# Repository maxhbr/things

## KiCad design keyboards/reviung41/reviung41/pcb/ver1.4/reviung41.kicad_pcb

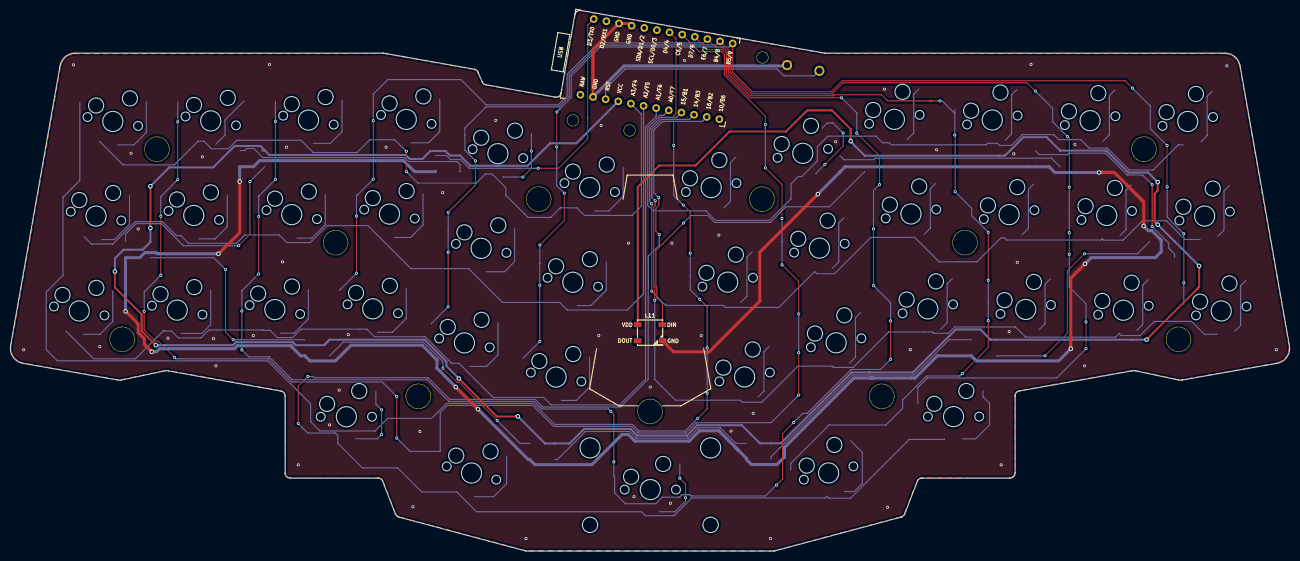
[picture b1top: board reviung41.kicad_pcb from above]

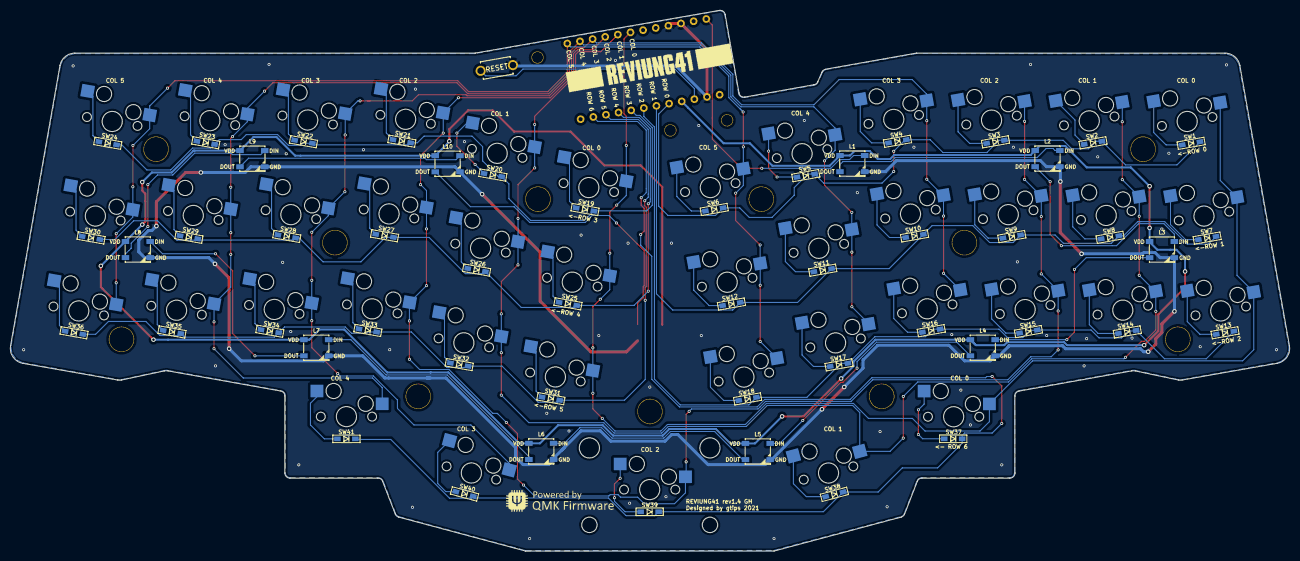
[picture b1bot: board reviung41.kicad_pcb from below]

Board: 2 copper layers, 253.3 x 107.1 mm, 109 parts (52 on the bottom side), 68 nets.

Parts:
D1, D2, D3, D4, D5, D6, D7, D8, D9, D10, D11, D12, D13, D14, D15, D16, D17, D18, D19, D20, D21, D22, D23, D24, D25, D26, D27, D28, D29, D30, D31, D32, D33, D34, D35, D36, D37, D38, D39, D40, D41: 1N4148W; D3_SMD_1side
H1: H1; HOLE
H2: H2; HOLE
H3: H3; HOLE
H4: H4; HOLE
H5: H5; HOLE
H6: H6; HOLE
H7: H7; HOLE
H8: H8; HOLE
H9: H9; HOLE
H10: H10; HOLE
H11: H11; HOLE
H12: H12; HOLE_2.2mm
H13: H13; HOLE_2.2mm
H14: H14; HOLE_2.2mm
L1, L2, L3, L4, L5, L6, L7, L8, L9, L10, L11: WS2812B; LED_WS2812B_PLCC4_5.0x5.0mm_P3.2mm
RESET1: SW_PUSH; ResetSW_1side
SW1, SW2, SW3, SW4, SW5, SW6, SW7, SW8, SW9, SW10, SW11, SW12, SW13, SW14, SW15, SW16, SW17, SW18, SW19, SW20, SW21, SW22, SW23, SW24, SW25, SW26, SW27, SW28, SW29, SW30, SW31, SW32, SW33, SW34, SW35, SW36, SW37, SW38, SW40, SW41: SW_PUSH; MXOnly-1U-Hotswap
SW39: SW_2U_PUSH; MXOnly-2U-Hotswap-ReversedStabilizers
U1: ProMicro

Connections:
GND: L1.3 (VSS), L2.3 (VSS), L3.3 (VSS), L4.3 (VSS), L5.3 (VSS), L6.3 (VSS), L7.3 (VSS), L8.3 (VSS), L9.3 (VSS), L10.3 (VSS), L11.3 (VSS), RESET1.2, U1.3 (GND), U1.4 (GND), U1.23 (GND)
LED: L1.4 (DIN), U1.1 (TX0/D3)
unnamed: D1.2 (A), SW1.2
unnamed: D2.2 (A), SW2.2
unnamed: D3.2 (A), SW3.2
unnamed: D4.2 (A), SW4.2
unnamed: D5.2 (A), SW5.2
unnamed: D6.2 (A), SW6.2
unnamed: D7.2 (A), SW7.2
unnamed: D8.2 (A), SW8.2
unnamed: D9.2 (A), SW9.2
unnamed: D10.2 (A), SW10.2
unnamed: D11.2 (A), SW11.2
unnamed: D12.2 (A), SW12.2
unnamed: D13.2 (A), SW13.2
unnamed: D14.2 (A), SW14.2
unnamed: D15.2 (A), SW15.2
unnamed: D16.2 (A), SW16.2
unnamed: D17.2 (A), SW17.2
unnamed: D18.2 (A), SW18.2
unnamed: D19.2 (A), SW19.2
unnamed: D20.2 (A), SW20.2
unnamed: D21.2 (A), SW21.2
unnamed: D22.2 (A), SW22.2
unnamed: D23.2 (A), SW23.2
unnamed: D24.2 (A), SW24.2
unnamed: D25.2 (A), SW25.2
unnamed: D26.2 (A), SW26.2
unnamed: D27.2 (A), SW27.2
unnamed: D28.2 (A), SW28.2
unnamed: D29.2 (A), SW29.2
unnamed: D30.2 (A), SW30.2
unnamed: D31.2 (A), SW31.2
unnamed: D32.2 (A), SW32.2
unnamed: D33.2 (A), SW33.2
unnamed: D34.2 (A), SW34.2
unnamed: D35.2 (A), SW35.2
unnamed: D36.2 (A), SW36.2
unnamed: D37.2 (A), SW37.2
unnamed: D38.2 (A), SW38.2
unnamed: D39.2 (A), SW39.2
unnamed: D40.2 (A), SW40.2
unnamed: D41.2 (A), SW41.2
unnamed: L1.2 (DOUT), L2.4 (DIN)
unnamed: L2.2 (DOUT), L3.4 (DIN)
unnamed: L3.2 (DOUT), L4.4 (DIN)
unnamed: L4.2 (DOUT), L5.4 (DIN)
unnamed: L5.2 (DOUT), L6.4 (DIN)
unnamed: L6.2 (DOUT), L7.4 (DIN)
unnamed: L7.2 (DOUT), L8.4 (DIN)
unnamed: L8.2 (DOUT), L9.4 (DIN)
unnamed: L10.2 (DOUT), L11.4 (DIN)
unnamed: L9.2 (DOUT), L10.4 (DIN)
VCC: L1.1 (VDD), L2.1 (VDD), L3.1 (VDD), L4.1 (VDD), L5.1 (VDD), L6.1 (VDD), L7.1 (VDD), L8.1 (VDD), L9.1 (VDD), L10.1 (VDD), L11.1 (VDD), U1.21 (VCC)
col0: SW1.1, SW7.1, SW13.1, SW19.1, SW25.1, SW31.1, SW37.1, U1.7 (4/D4)
col1: SW2.1, SW8.1, SW14.1, SW20.1, SW26.1, SW32.1, SW38.1, U1.8 (5/C6)
col2: SW3.1, SW9.1, SW15.1, SW21.1, SW27.1, SW33.1, SW39.1, U1.9 (6/D7)
col3: SW4.1, SW10.1, SW16.1, SW22.1, SW28.1, SW34.1, SW40.1, U1.10 (7/E6)
col4: SW5.1, SW11.1, SW17.1, SW23.1, SW29.1, SW35.1, SW41.1, U1.11 (8/B4)
col5: SW6.1, SW12.1, SW18.1, SW24.1, SW30.1, SW36.1, U1.12 (9/B5)
reset: RESET1.1, U1.22 (RST)
row0: D1.1 (K), D2.1 (K), D3.1 (K), D4.1 (K), D5.1 (K), D6.1 (K), U1.20 (F4/A3)
row1: D7.1 (K), D8.1 (K), D9.1 (K), D10.1 (K), D11.1 (K), D12.1 (K), U1.19 (F5/A2)
row2: D13.1 (K), D14.1 (K), D15.1 (K), D16.1 (K), D17.1 (K), D18.1 (K), U1.18 (F6/A1)
row3: D19.1 (K), D20.1 (K), D21.1 (K), D22.1 (K), D23.1 (K), D24.1 (K), U1.17 (F7/A0)
row4: D25.1 (K), D26.1 (K), D27.1 (K), D28.1 (K), D29.1 (K), D30.1 (K), U1.16 (B1/15)
row5: D31.1 (K), D32.1 (K), D33.1 (K), D34.1 (K), D35.1 (K), D36.1 (K), U1.15 (B3/14)
row6: D37.1 (K), D38.1 (K), D39.1 (K), D40.1 (K), D41.1 (K), U1.14 (B2/16)

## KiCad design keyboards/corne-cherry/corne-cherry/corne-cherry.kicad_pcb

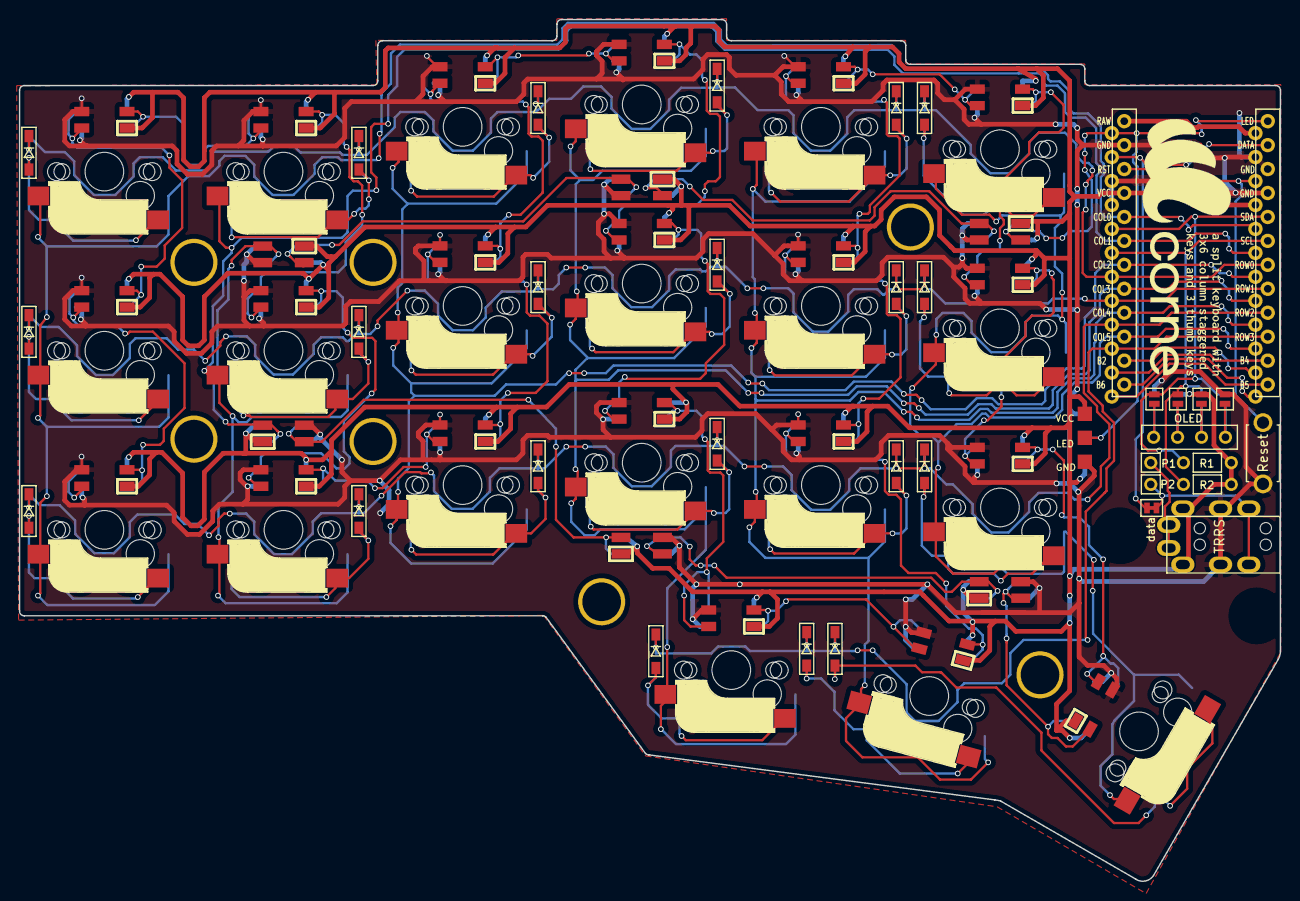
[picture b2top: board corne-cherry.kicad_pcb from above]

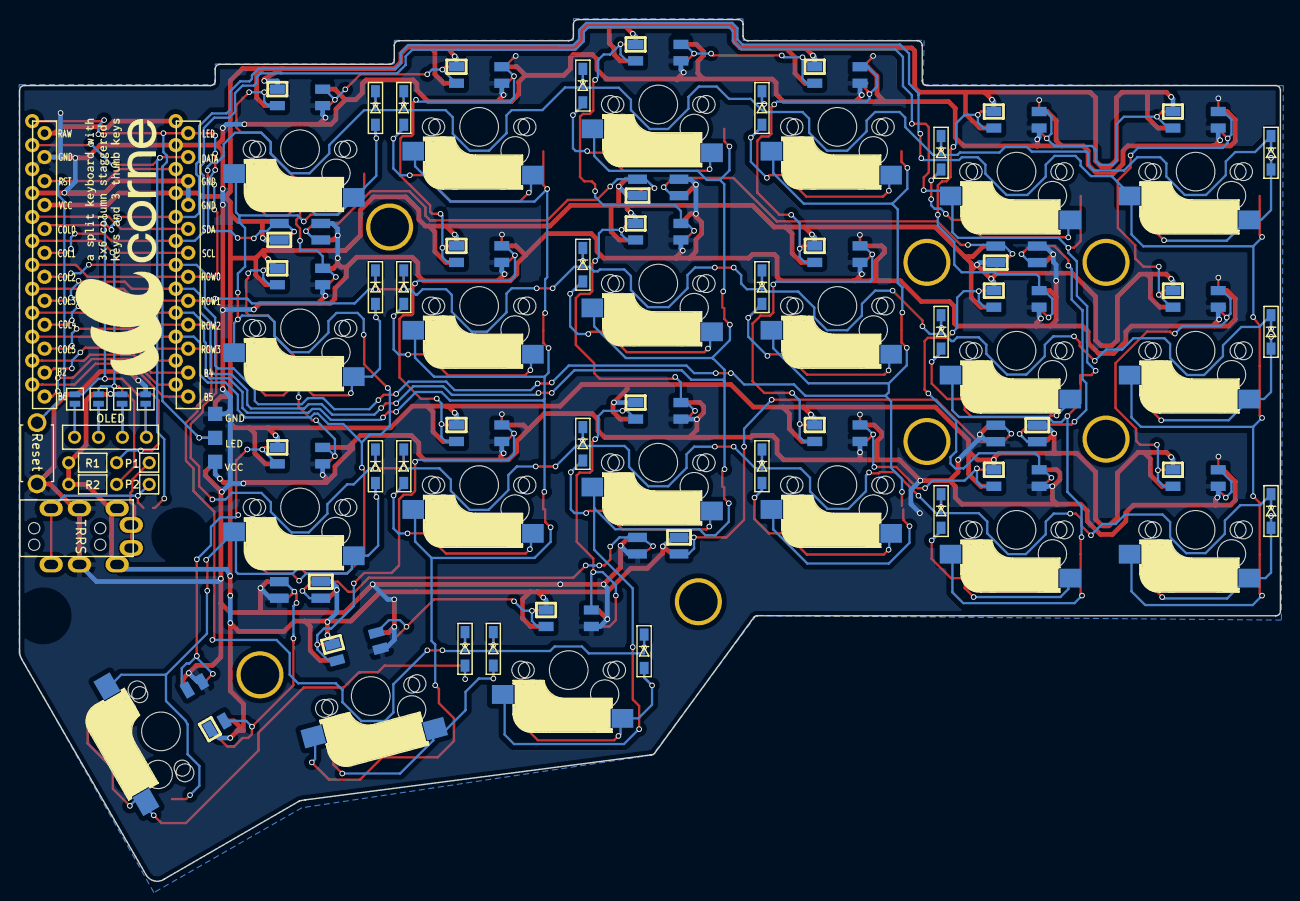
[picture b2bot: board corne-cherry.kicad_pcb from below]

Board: 2 copper layers, 133.8 x 91.4 mm, 87 parts (4 on the bottom side), 70 nets.

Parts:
D1, D2, D3, D4, D5, D6, D7, D8, D9, D10, D11, D12, D13, D14, D15, D16, D17, D18, D19, D20, D21: D; D3_SMD
J3: LED; StripLED_rev
JP2, JP3, JP4, JP5, JP6, JP7, JP8, JP9: Jumper
L1, L2, L3, L4, L5, L6, L7, L8, L9, L10, L11, L12, L13, L14, L15, L16, L17, L18, L19, L20, L21: SK6812MINI; SK6812MINI_rev
L22, L23, L24, L25, L26, L27: SK6812MINI; SK6812MINI_underglow_rev
OLED: OLED
P1, P2: i2c-pin; 1pin_conn
R1, R2: R
RSW1: Reset; ResetSW
SW1, SW2, SW3, SW4, SW5, SW6, SW7, SW8, SW9, SW10, SW11, SW12, SW13, SW14, SW15, SW16, SW17, SW18, SW19, SW20: SW_PUSH; CherryMX_MidHeight_Hotswap
SW21: SW_PUSH; CherryMX_MidHeight_Hotswap_1.5u
TRRS: MJ-4PP-9
U1: ProMicro; ProMicro_v2
data: JPC2

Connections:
GND: J3.1, JP2.1, JP9.1, L1.2, L2.2, L3.2, L4.2, L5.2, L6.2, L7.2, L8.2, L9.2, L10.2, L11.2, L12.2, L13.2, L14.2, L15.2, L16.2, L17.2, L18.2, L19.2, L20.2, L21.2, L22.2, L23.2, L24.2, L25.2, L26.2, L27.2, RSW1.2, TRRS.C, U1.3, U1.4, U1.23
LED: J3.2, L24.3, U1.1
unnamed: D1.2, SW1.2
unnamed: D2.2, SW2.2
unnamed: D3.2, SW3.2
unnamed: D4.2, SW4.2
unnamed: D5.2, SW5.2
unnamed: D6.2, SW6.2
unnamed: D7.2, SW7.2
unnamed: D8.2, SW8.2
unnamed: D9.2, SW9.2
unnamed: D10.2, SW10.2
unnamed: D11.2, SW11.2
unnamed: D12.2, SW12.2
unnamed: D13.2, SW13.2
unnamed: D14.2, SW14.2
unnamed: D15.2, SW15.2
unnamed: D16.2, SW16.2
unnamed: D17.2, SW17.2
unnamed: D18.2, SW18.2
unnamed: D19.2, SW19.2
unnamed: D20.2, SW20.2
unnamed: D21.2, SW21.2
unnamed: P1.1, TRRS.A
unnamed: P2.1, TRRS.B, data.2
unnamed: JP5.2, JP9.2, OLED.1
unnamed: JP4.2, JP8.2, OLED.2
unnamed: JP3.2, JP7.2, OLED.3
unnamed: JP2.2, JP6.2, OLED.4
unnamed: L1.1, L7.3
unnamed: L1.3, L2.1
unnamed: L2.3, L8.1
unnamed: L3.1, L9.3
unnamed: L3.3, L4.1
unnamed: L5.3, L6.1
unnamed: L4.3, L10.1
unnamed: L10.3, L16.1
unnamed: L11.1, L17.3
unnamed: L5.1, L11.3
unnamed: L6.3, L12.1
unnamed: L12.3, L18.1
unnamed: L7.1, L13.3
unnamed: L8.3, L14.1
unnamed: L14.3, L15.1
unnamed: L9.1, L15.3
unnamed: L16.3, L19.1
unnamed: L17.1, L20.3
unnamed: L18.3, L21.1
unnamed: L19.3, L20.1
unnamed: L21.3, L27.1
unnamed: L22.1, L25.3
unnamed: L22.3, L23.1
unnamed: L23.3, L24.1
unnamed: L25.1, L26.3
unnamed: L26.1, L27.3
SCL: JP4.1, JP7.1, R2.2, U1.6
SDA: JP5.1, JP6.1, R1.2, U1.5
VCC: J3.3, JP3.1, JP8.1, L1.4, L2.4, L3.4, L4.4, L5.4, L6.4, L7.4, L8.4, L9.4, L10.4, L11.4, L12.4, L13.4, L14.4, L15.4, L16.4, L17.4, L18.4, L19.4, L20.4, L21.4, L22.4, L23.4, L24.4, L25.4, L26.4, L27.4, R1.1, R2.1, TRRS.D, U1.21
col0: SW1.1, SW7.1, SW13.1, U1.20
col1: SW2.1, SW8.1, SW14.1, U1.19
col2: SW3.1, SW9.1, SW15.1, U1.18
col3: SW4.1, SW10.1, SW16.1, SW19.1, U1.17
col4: SW5.1, SW11.1, SW17.1, SW20.1, U1.16
col5: SW6.1, SW12.1, SW18.1, SW21.1, U1.15
data: U1.2, data.1
reset: RSW1.1, U1.22
row0: D1.1, D2.1, D3.1, D4.1, D5.1, D6.1, U1.7
row1: D7.1, D8.1, D9.1, D10.1, D11.1, D12.1, U1.8
row2: D13.1, D14.1, D15.1, D16.1, D17.1, D18.1, U1.9
row3: D19.1, D20.1, D21.1, U1.10

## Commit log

2021-11-15 add Nidavellir
2021-11-17 +v2 +v3
2021-11-17 add PNGs
2021-11-18 add stls and build script
2021-11-18 update STLs and ceate FCStd
2021-11-18 update: walls are now thinner
2021-11-18 udate and rebuild
2021-11-19 update and rebuild
2021-11-19 make base of box thinner
2021-11-19 add readme
2021-11-20 add NidavellirComplete to show also other stls
2021-11-20 make colors more prominent
2021-11-20 add more renderings
2021-11-20 udate README
2021-11-20 add ttf font
2021-11-20 rebuild
2021-11-20 recreate and rebuild
2021-11-22 more space for coins, and potentially to many supports
2021-11-22 update README and tag
2021-11-22 make height parametric
2021-11-22 move one image up
2021-11-24 update builds
2021-11-28 font in bold
2021-11-29 subtract coins last
2021-12-02 recompute
2021-12-05 add tbh
2021-12-12 add stuffholder
2021-12-22 work on stuffholder
2021-12-22 add v1b
2021-12-22 add v1c :)
2021-12-23 minor improvements
2021-12-23 now it needs support?
2021-12-23 add url
2021-12-23 update stls and add boxes
2021-12-23 add screenshot
2021-12-23 add lables
2021-12-24 add imperium WIP
2021-12-25 RaidersOfScythia
2021-12-25 update RoS
2021-12-26 Imperium
2021-12-27 add script to build all stls in parallel
2021-12-27 rebuild (again)
2021-12-27 add readme to imperium
2021-12-27 ignore ast files
2021-12-30 wip 2Car
2022-01-01 add triCar
2022-01-02 build 2Car
2022-01-02 move stuff to subfolders
2022-01-06 update 2car
2022-01-24 update and recompute
2022-01-24 add full stl
2022-01-24 add slim common
2022-03-08 add reliasecase
2022-04-08 add nyx keeb case
2022-04-08 add font
2022-04-09 fix typo
2022-04-12 add redox and kyria case
2022-04-14 add saltstand
2022-04-18 work on v2
2022-04-23 add rotStop
2022-05-02 Squashed 'keyboards/reviung41/reviung41/' content from commit d79e0cb
    git-subtree-dir: keyboards/reviung41/reviung41
    git-subtree-split: d79e0cb2763772315a96caf19aaef780e80670ce
2022-05-02 add reviung41 following https://stackoverflow.com/questions/23937436/add-subdirectory-of-remote-repo-with-git-subtree
2022-05-03 add reviung41 case
2022-05-04 fix missing stab
2022-05-10 Squashed 'keyboards/corne-cherry/corne-cherry/' content from commit 20972da
    git-subtree-dir: keyboards/corne-cherry/corne-cherry
    git-subtree-split: 20972da3c2937e4cbff60f762cc8eb94b5dc147a
2022-05-10 add corne cherry with license
2022-05-10 switch to right corne-cherry
2022-05-10 Squashed 'keyboards/corne-cherry/corne-cherry/' content from commit 384d2ed
    git-subtree-dir: keyboards/corne-cherry/corne-cherry
    git-subtree-split: 384d2edbc34e5fd442e81eb0d2035c94f3a97cfb
2022-05-10 Squashed 'keyboards/corne-cherry/corne-cherry/' content from commit a5f2f59
    git-subtree-dir: keyboards/corne-cherry/corne-cherry
    git-subtree-split: a5f2f5936893a938dc1fc016ffd1eeba467d9fb6
2022-05-10 add corne .stls
2022-05-10 regenerate stls
2022-05-10 rebuild STLs
2022-05-10 update gitignore
2022-05-16 Squashed 'Round-Anything/' content from commit 980948b
    git-subtree-dir: Round-Anything
    git-subtree-split: 980948b31cc11edbe5376ac70ba6aba7bd71c578
2022-05-16 add radlands
2022-05-16 add coin
2022-06-26 fix radlands
2022-08-07 add fbh
2022-08-17 add tybor
2022-08-17 update tybor
2022-08-18 snapshot genbox script
2022-08-18 add mottainai
2023-03-26 some stuff
2023-12-09 add rail mounting hardware
2023-12-10 mirror fun?
2023-12-13 add stls
2023-12-19 1.1.3
2024-01-08 macro rail moved to https://github.com/maxhbr/zephyr-rail
